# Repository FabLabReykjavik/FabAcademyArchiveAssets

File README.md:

# FabAcademyArchiveAssets
All files and assets from the Fab Academy Archive

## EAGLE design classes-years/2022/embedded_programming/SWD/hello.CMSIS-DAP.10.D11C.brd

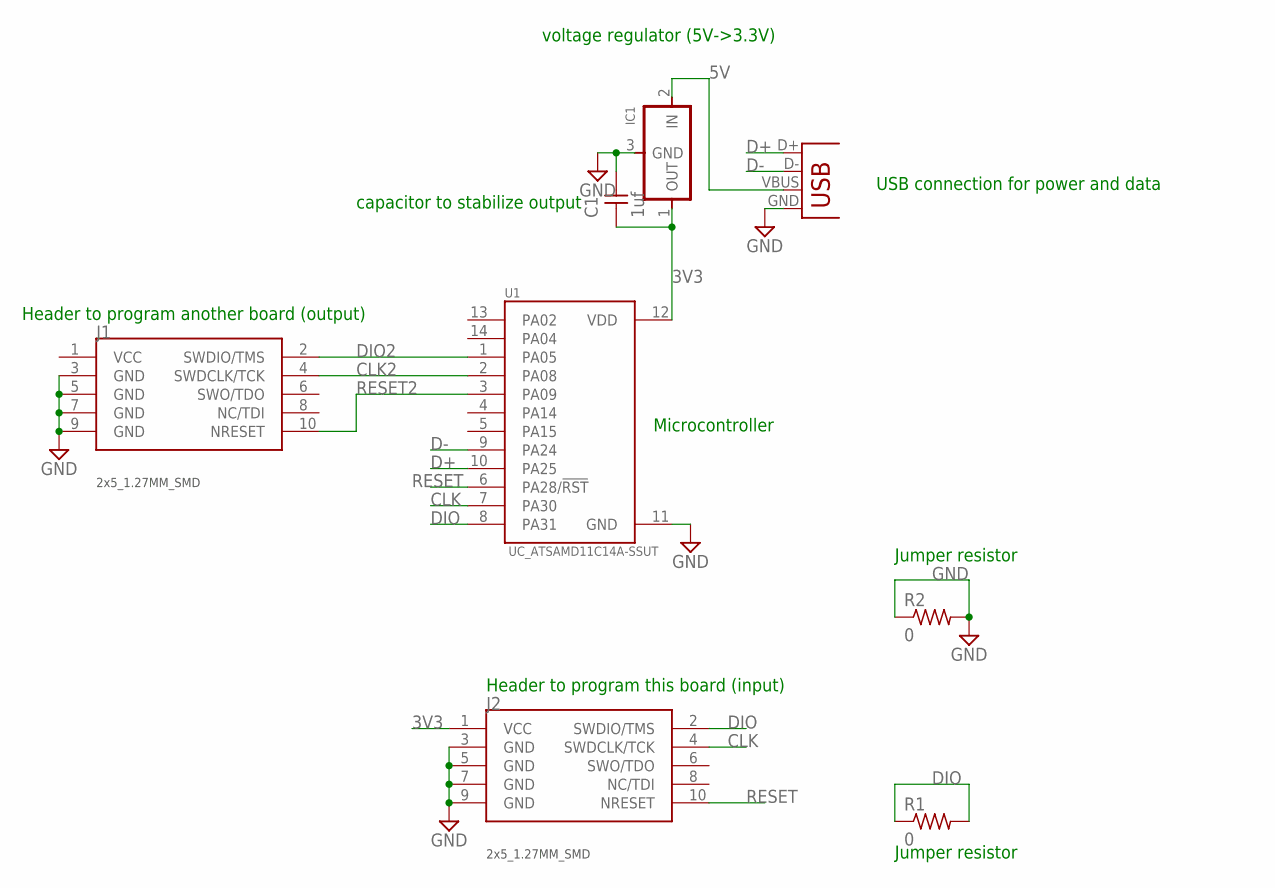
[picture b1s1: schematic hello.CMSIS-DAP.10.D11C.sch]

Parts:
C1: 1uf; C1206FAB
IC1: VR_REGULATOR-SOT23SOT23; SOT23
J1, J2: CONN_05X2_ARM_DEBUGSMD; 2X5_1.27MM_SMD
R1, R2: 0; R1206FAB
U1: UC_ATSAMD11C14A-SSUT; SOIC127P600X160-14N
X1: CONN_USB-A-LC; USB-A_LC

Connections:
3V3: C1.1, IC1.1 (OUT), J2.1 (VCC), U1.12 (VDD)
5V: IC1.2 (IN), X1.VBUS
CLK: J2.4 (SWDCLK/TCK), U1.7 (PA30)
CLK2: J1.4 (SWDCLK/TCK), U1.2 (PA08)
D+: U1.10 (PA25), X1.D+
D-: U1.9 (PA24), X1.D-
DIO: J2.2 (SWDIO/TMS), R1.1, R1.2, U1.8 (PA31)
DIO2: J1.2 (SWDIO/TMS), U1.1 (PA05)
GND: C1.2, IC1.3 (GND), J1.3 (GND), J1.5 (GND), J1.7 (GND), J1.9 (GND), J2.3 (GND), J2.5 (GND), J2.7 (GND), J2.9 (GND), R2.1, R2.2, U1.11 (GND), X1.GND
RESET: J2.10 (NRESET), U1.6 (PA28/!RST)
RESET2: J1.10 (NRESET), U1.3 (PA09)

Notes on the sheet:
Jumper resistor
Header to program this board (input)
Header to program another board (output)
Microcontroller
USB connection for power and data
voltage regulator (5V->3.3V)
capacitor to stabilize output

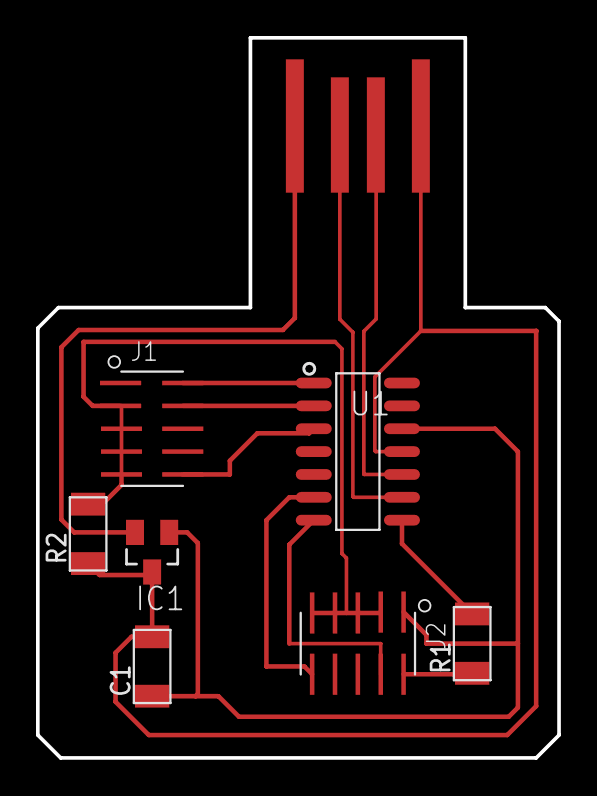
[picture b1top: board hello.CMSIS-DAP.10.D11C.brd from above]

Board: 2 copper layers, 29.0 x 40.0 mm, 8 parts (0 on the bottom side), 11 nets.

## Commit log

2025-11-07 all assets from FabAcademy - classes-master - Nov 7 2025
2025-11-10 adding files unique to 2012, 2013, 2014, 2015, 2016
2025-11-10 adding all index.html for 2012, fixing report
2025-11-10 adding all index.html for 2013, fixing report
2025-11-10 adding all index.html for 2014, fixing report
2025-11-10 adding all index.html for 2015, fixing report
2025-11-10 adding all index.html for 2016, fixing report
2025-11-10 adding all index.html for 2017, fixing report
2025-11-10 adding 2018 assets
2025-11-10 adding 2019 assets
2025-11-10 adding 2020
2025-11-10 adding 2021 assets
2025-11-11 adding 2022, 2023, 2024 assets
